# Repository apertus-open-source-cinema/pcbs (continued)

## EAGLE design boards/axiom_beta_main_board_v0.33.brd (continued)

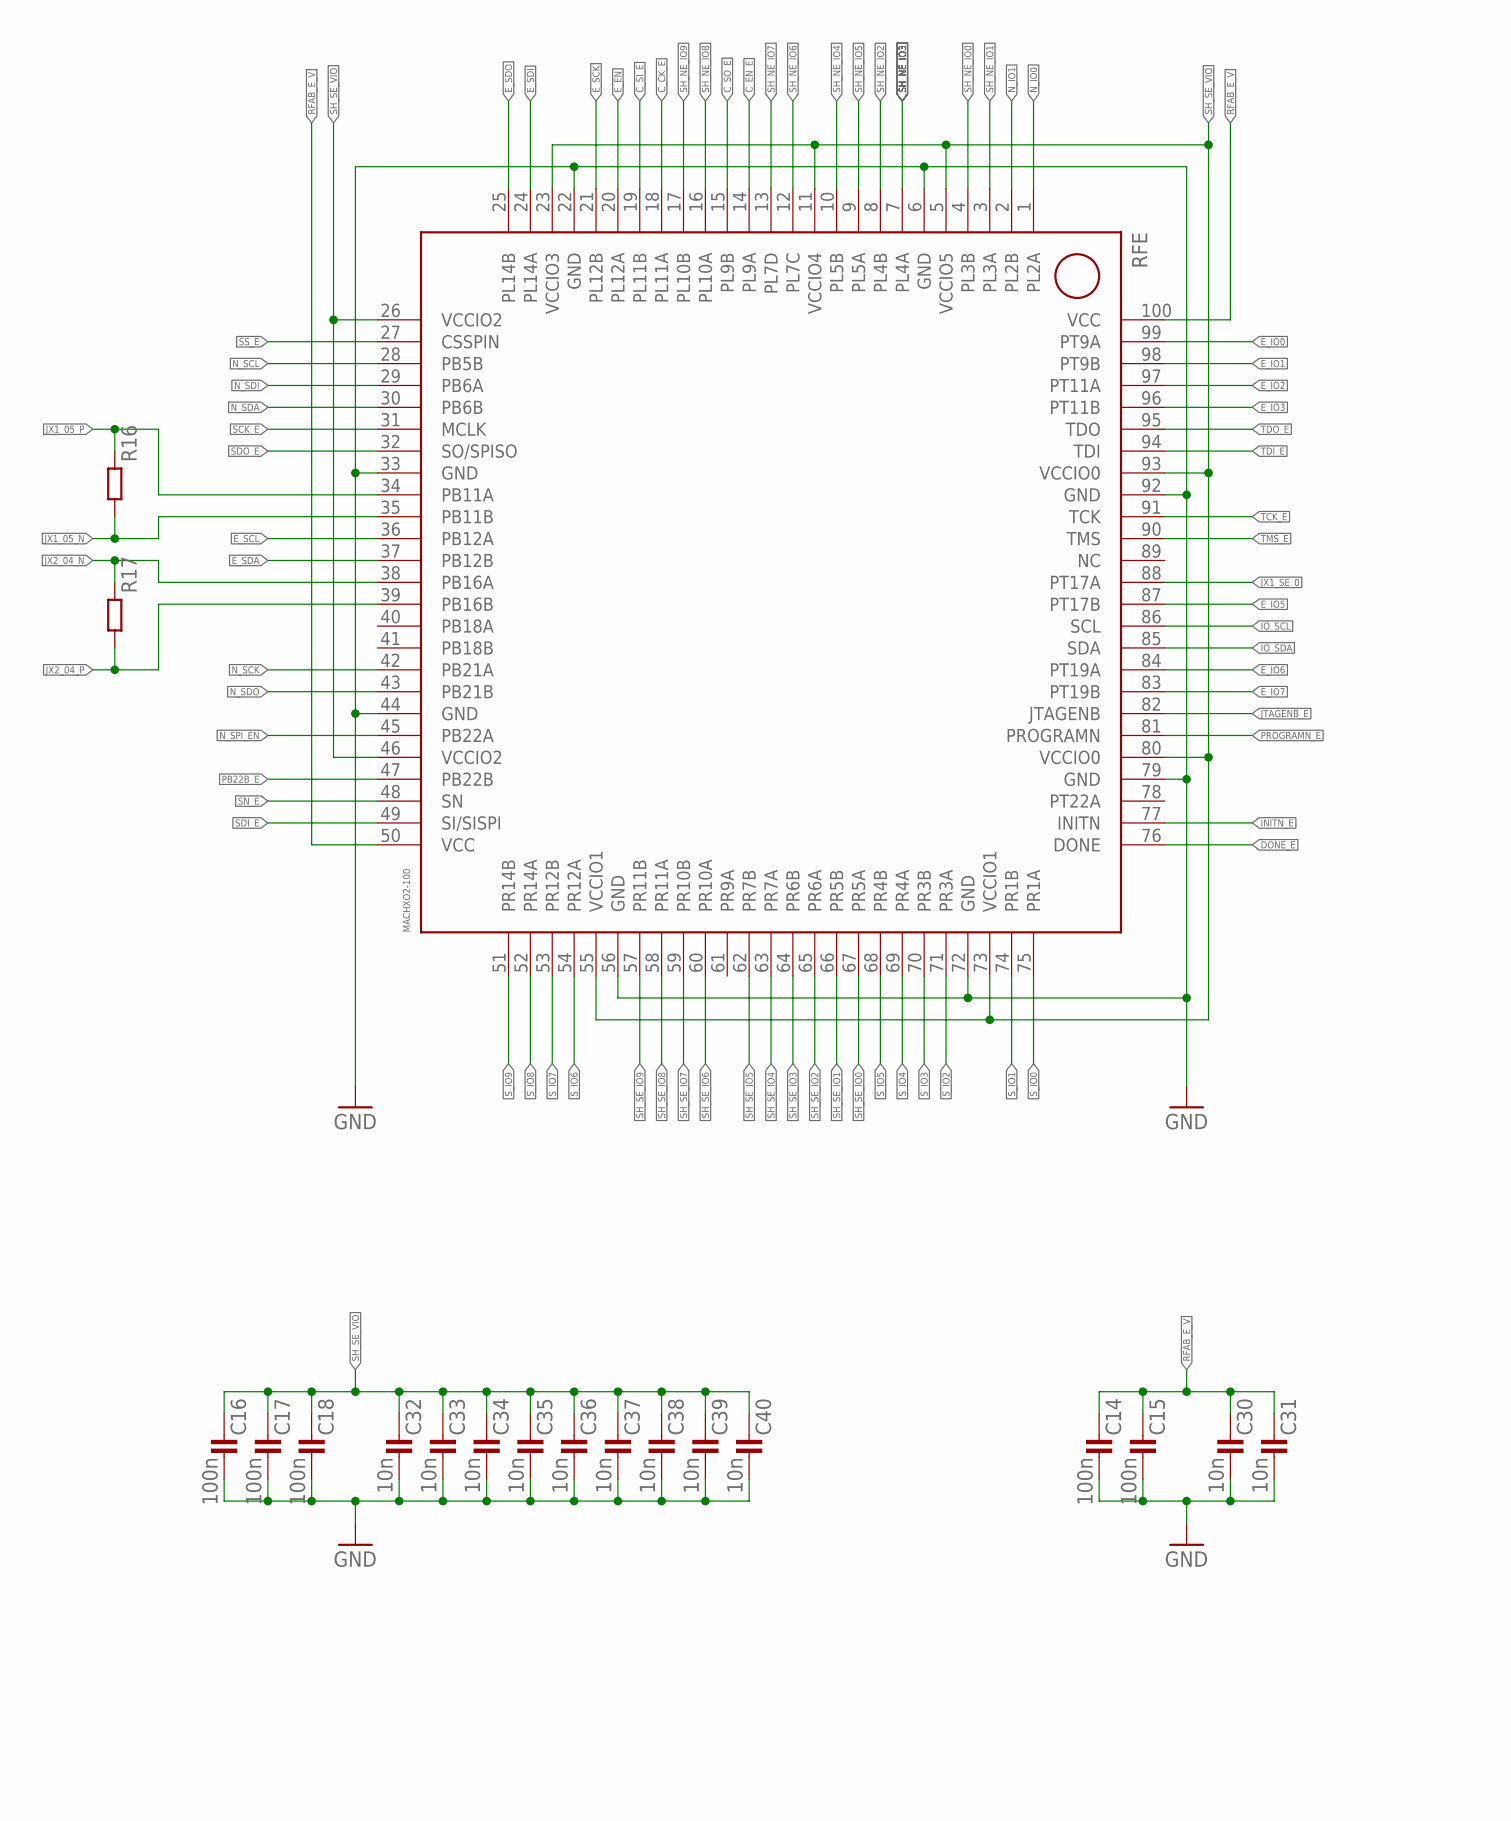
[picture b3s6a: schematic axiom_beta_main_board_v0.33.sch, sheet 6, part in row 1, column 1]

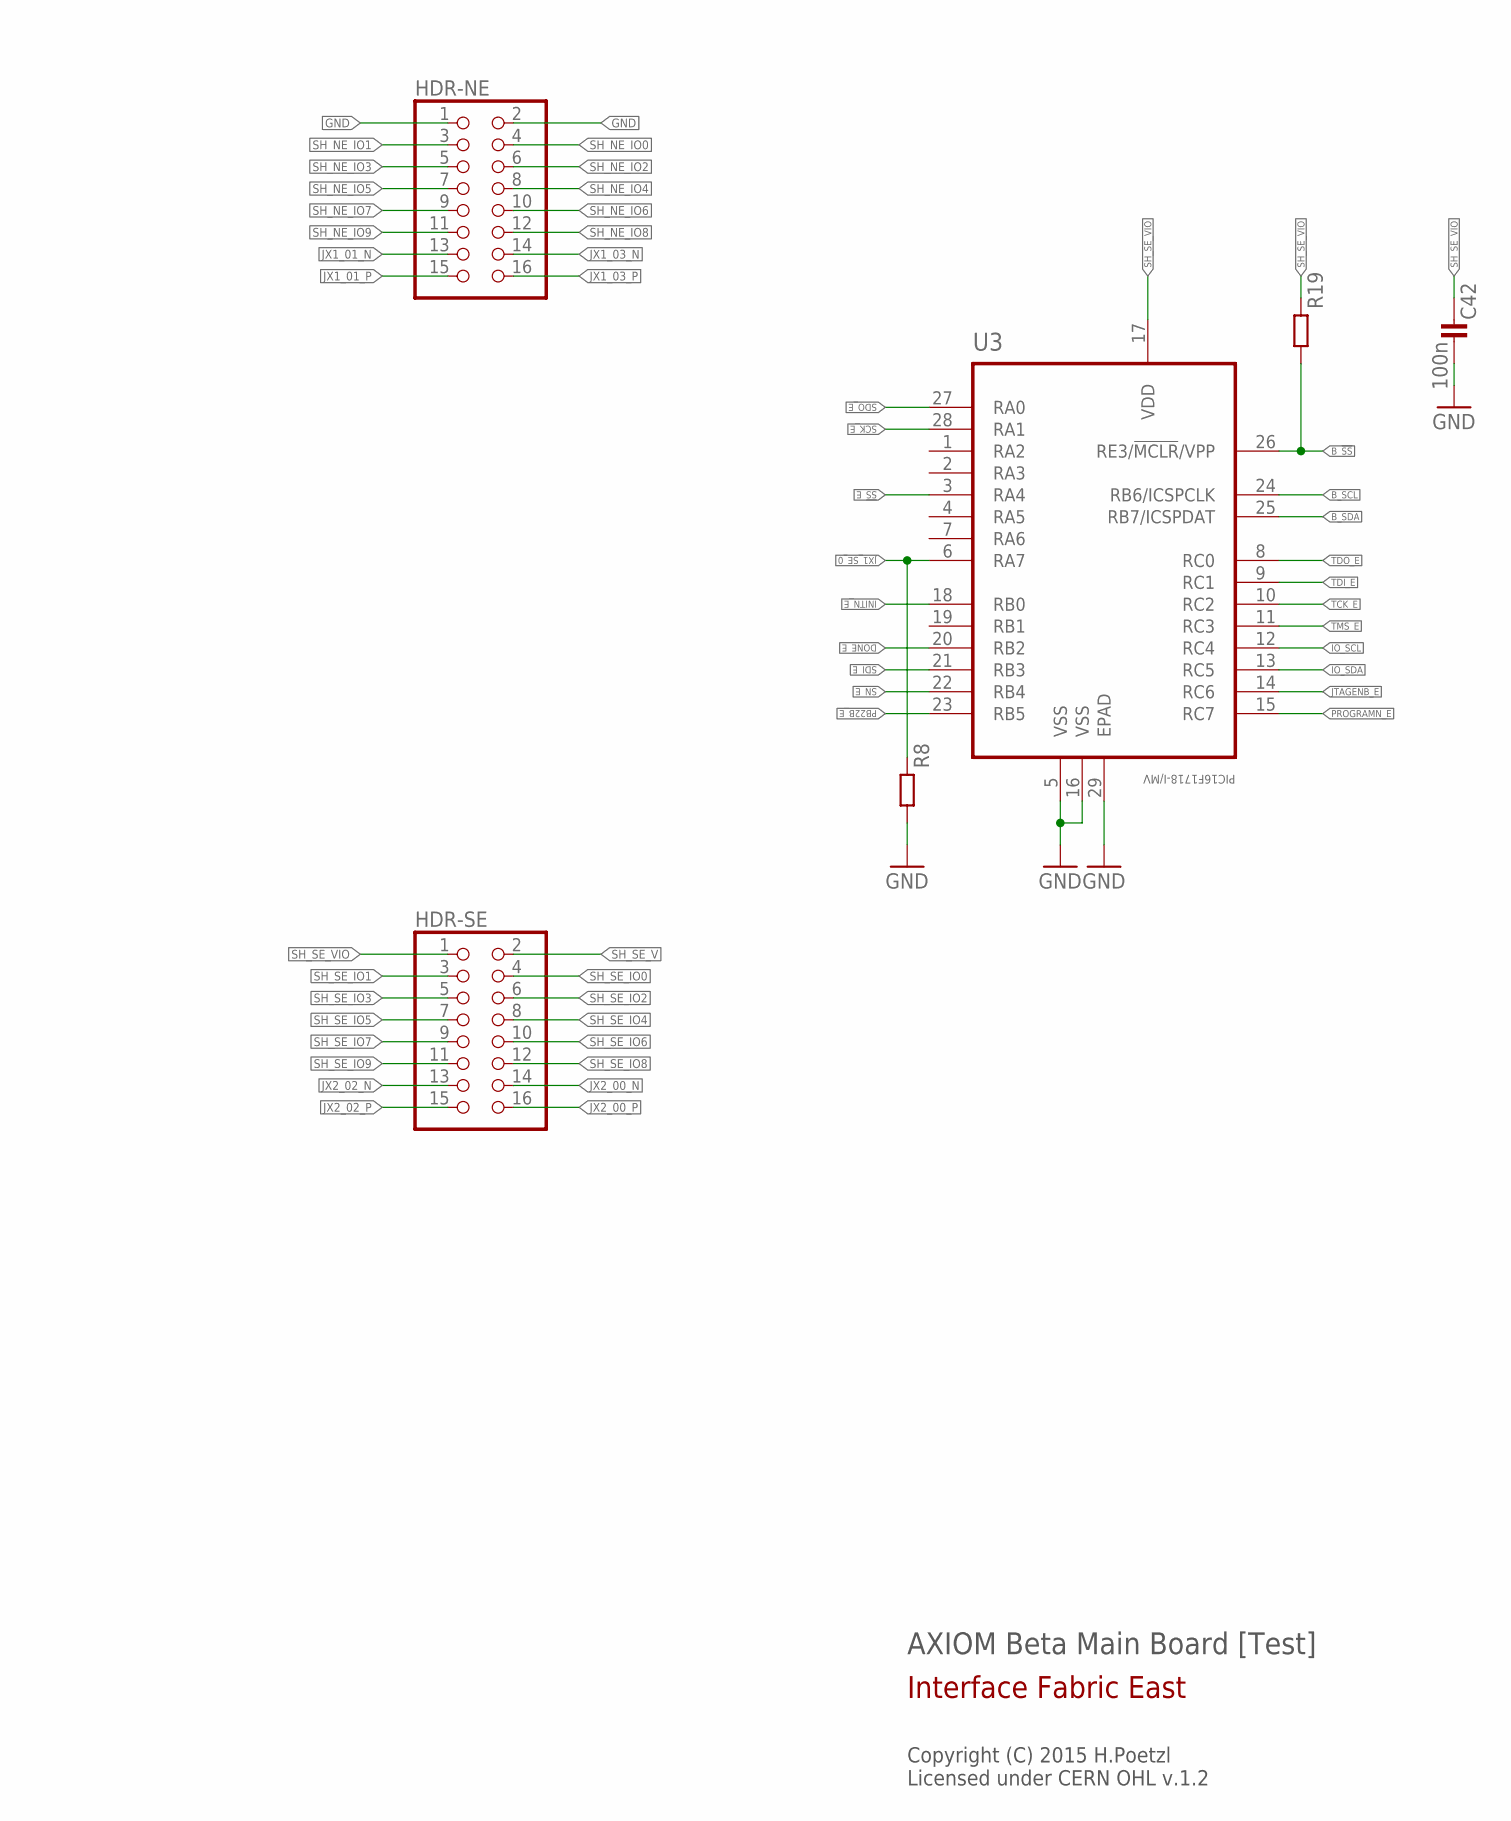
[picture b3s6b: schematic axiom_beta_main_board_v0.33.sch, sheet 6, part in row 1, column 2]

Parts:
C14, C15, C16, C17, C18, C42: 100n; 0402-B
C30, C31, C32, C33, C34, C35, C36, C37, C38, C39, C40: 10n; 0402-B
HDR-NE: PINHD-2X08_2.00_LPR; 62101621821
HDR-SE: PINHD-2X08_2.00_LPR; 62101621821
R8, R19: R0402-B; 0402-B
R16, R17: R0201-B; 0201-B
RFE: MACHXO2-100; MACHXO2-100TQFP
U3: PIC16F1718-I/MV; QFN40P400X400X55-29N

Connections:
!SS!_E: RFE.27 (CSSPIN), U3.3 (RA4)
B_!SS: R19.2, U3.26 (RE3/!MCLR!/VPP); also elsewhere on the board
B_SCL: U3.24 (RB6/ICSPCLK); also elsewhere on the board
B_SDA: U3.25 (RB7/ICSPDAT); also elsewhere on the board
C_CK_E: RFE.18 (PL11A); also elsewhere on the board
C_EN_E: RFE.14 (PL9A); also elsewhere on the board
C_SI_E: RFE.19 (PL11B); also elsewhere on the board
C_SO_E: RFE.15 (PL9B); also elsewhere on the board
DONE_E: RFE.76 (DONE), U3.20 (RB2)
E_EN: RFE.20 (PL12A); also elsewhere on the board
E_IO0: RFE.99 (PT9A)
E_IO1: RFE.98 (PT9B)
E_IO2: RFE.97 (PT11A)
E_IO3: RFE.96 (PT11B)
E_IO5: RFE.87 (PT17B)
E_IO6: RFE.84 (PT19A)
E_IO7: RFE.83 (PT19B)
E_SCK: RFE.21 (PL12B); also elsewhere on the board
E_SCL: RFE.36 (PB12A); also elsewhere on the board
E_SDA: RFE.37 (PB12B); also elsewhere on the board
E_SDI: RFE.24 (PL14A); also elsewhere on the board
E_SDO: RFE.25 (PL14B); also elsewhere on the board
GND: C14.2, C15.2, C16.2, C17.2, C18.2, C30.2, C31.2, C32.2, C33.2, C34.2, C35.2, C36.2, C37.2, C38.2, C39.2, C40.2, C42.2, HDR-NE.1, HDR-NE.2, R8.2, RFE.6 (GND), RFE.22 (GND), RFE.33 (GND), RFE.44 (GND), RFE.56 (GND), RFE.72 (GND), RFE.79 (GND), RFE.92 (GND), U3.5 (VSS), U3.16 (VSS), U3.29 (EPAD); also elsewhere on the board
INITN_E: RFE.77 (INITN), U3.18 (RB0)
IO_SCL: RFE.86 (SCL), U3.12 (RC4)
IO_SDA: RFE.85 (SDA), U3.13 (RC5)
JTAGENB_E: RFE.82 (JTAGENB), U3.14 (RC6)
JX1_01_N: HDR-NE.13; also elsewhere on the board
JX1_01_P: HDR-NE.15; also elsewhere on the board
JX1_03_N: HDR-NE.14; also elsewhere on the board
JX1_03_P: HDR-NE.16; also elsewhere on the board
JX1_05_N: R16.2, RFE.35 (PB11B); also elsewhere on the board
JX1_05_P: R16.1, RFE.34 (PB11A); also elsewhere on the board
JX1_SE_0: R8.1, RFE.88 (PT17A), U3.6 (RA7); also elsewhere on the board
JX2_00_N: HDR-SE.14; also elsewhere on the board
JX2_00_P: HDR-SE.16; also elsewhere on the board
JX2_02_N: HDR-SE.13; also elsewhere on the board
JX2_02_P: HDR-SE.15; also elsewhere on the board
JX2_04_N: R17.1, RFE.38 (PB16A); also elsewhere on the board
JX2_04_P: R17.2, RFE.39 (PB16B); also elsewhere on the board
N_IO0: RFE.1 (PL2A); also elsewhere on the board
N_IO1: RFE.2 (PL2B)
N_SCK: RFE.42 (PB21A); also elsewhere on the board
N_SCL: RFE.28 (PB5B); also elsewhere on the board
N_SDA: RFE.30 (PB6B); also elsewhere on the board
N_SDI: RFE.29 (PB6A); also elsewhere on the board
N_SDO: RFE.43 (PB21B); also elsewhere on the board
N_SPI_EN: RFE.45 (PB22A); also elsewhere on the board
PB22B_E: RFE.47 (PB22B), U3.23 (RB5)
PROGRAMN_E: RFE.81 (PROGRAMN), U3.15 (RC7)
RFAB_E_V: C14.1, C15.1, C30.1, C31.1, RFE.50 (VCC), RFE.100 (VCC); also elsewhere on the board
SCK_E: RFE.31 (MCLK), U3.28 (RA1)
SDI_E: RFE.49 (SI/SISPI), U3.21 (RB3)
SDO_E: RFE.32 (SO/SPISO), U3.27 (RA0)
SH_NE_IO0: HDR-NE.4, RFE.4 (PL3B)
SH_NE_IO1: HDR-NE.3, RFE.3 (PL3A)
SH_NE_IO2: HDR-NE.6, RFE.8 (PL4B)
SH_NE_IO3: HDR-NE.5, RFE.7 (PL4A)
SH_NE_IO4: HDR-NE.8, RFE.10 (PL5B)
SH_NE_IO5: HDR-NE.7, RFE.9 (PL5A)
SH_NE_IO6: HDR-NE.10, RFE.12 (PL7C)
SH_NE_IO7: HDR-NE.9, RFE.13 (PL7D)
SH_NE_IO8: HDR-NE.12, RFE.16 (PL10A)
SH_NE_IO9: HDR-NE.11, RFE.17 (PL10B)
SH_SE_IO0: HDR-SE.4, RFE.67 (PR5A)
SH_SE_IO1: HDR-SE.3, RFE.66 (PR5B)
SH_SE_IO2: HDR-SE.6, RFE.65 (PR6A)
SH_SE_IO3: HDR-SE.5, RFE.64 (PR6B)
SH_SE_IO4: HDR-SE.8, RFE.63 (PR7A)
SH_SE_IO5: HDR-SE.7, RFE.62 (PR7B)
SH_SE_IO6: HDR-SE.10, RFE.60 (PR10A)
SH_SE_IO7: HDR-SE.9, RFE.59 (PR10B)
SH_SE_IO8: HDR-SE.12, RFE.58 (PR11A)
SH_SE_IO9: HDR-SE.11, RFE.57 (PR11B)
SH_SE_V: HDR-SE.2; also elsewhere on the board
SH_SE_VIO: C16.1, C17.1, C18.1, C32.1, C33.1, C34.1, C35.1, C36.1, C37.1, C38.1, C39.1, C40.1, C42.1, HDR-SE.1, R19.1, RFE.5 (VCCIO5), RFE.11 (VCCIO4), RFE.23 (VCCIO3), RFE.26 (VCCIO2), RFE.46 (VCCIO2), RFE.55 (VCCIO1), RFE.73 (VCCIO1), RFE.80 (VCCIO0), RFE.93 (VCCIO0), U3.17 (VDD); also elsewhere on the board
SN_E: RFE.48 (SN), U3.22 (RB4)
S_IO0: RFE.75 (PR1A); also elsewhere on the board
S_IO1: RFE.74 (PR1B)
S_IO2: RFE.71 (PR3A)
S_IO3: RFE.70 (PR3B)
S_IO4: RFE.69 (PR4A)
S_IO5: RFE.68 (PR4B)
S_IO6: RFE.54 (PR12A)
S_IO7: RFE.53 (PR12B)
S_IO8: RFE.52 (PR14A)
S_IO9: RFE.51 (PR14B)
TCK_E: RFE.91 (TCK), U3.10 (RC2)
TDI_E: RFE.94 (TDI), U3.9 (RC1)
TDO_E: RFE.95 (TDO), U3.8 (RC0)
TMS_E: RFE.90 (TMS), U3.11 (RC3)

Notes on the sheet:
AXIOM Beta Main Board [Test]
Copyright (C) 2015 H.Poetzl Licensed under CERN OHL v.1.2
Interface Fabric East

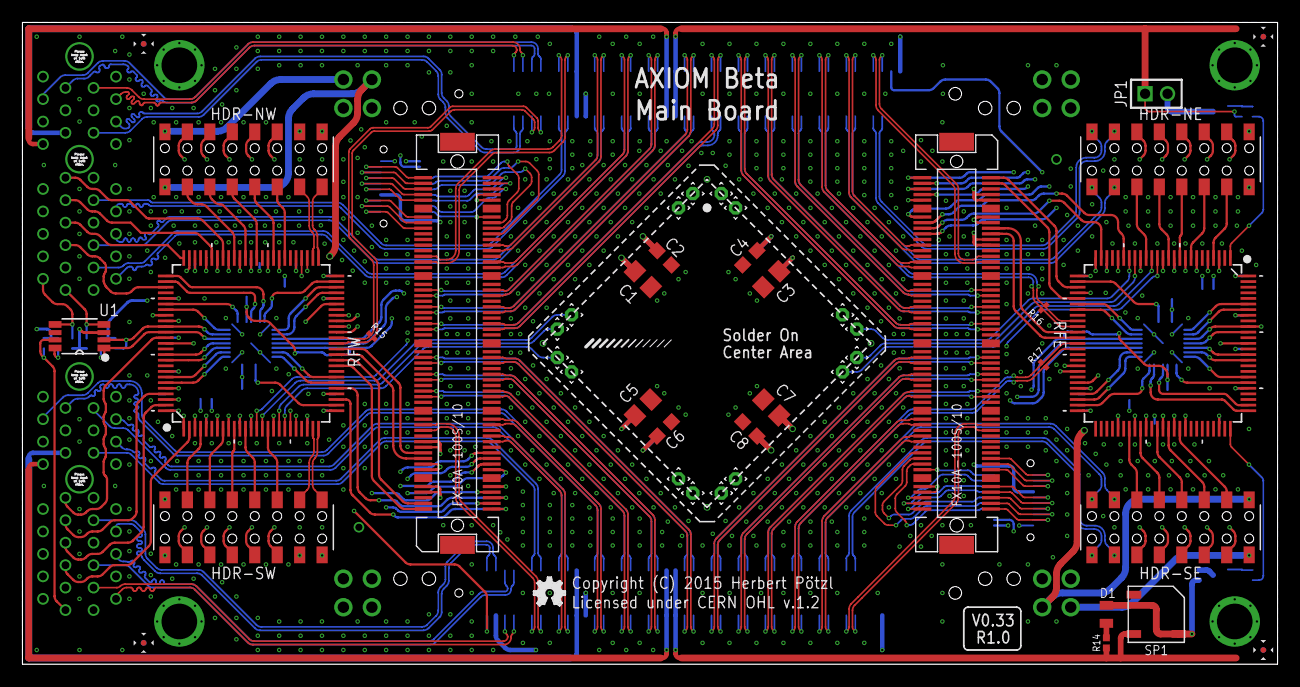
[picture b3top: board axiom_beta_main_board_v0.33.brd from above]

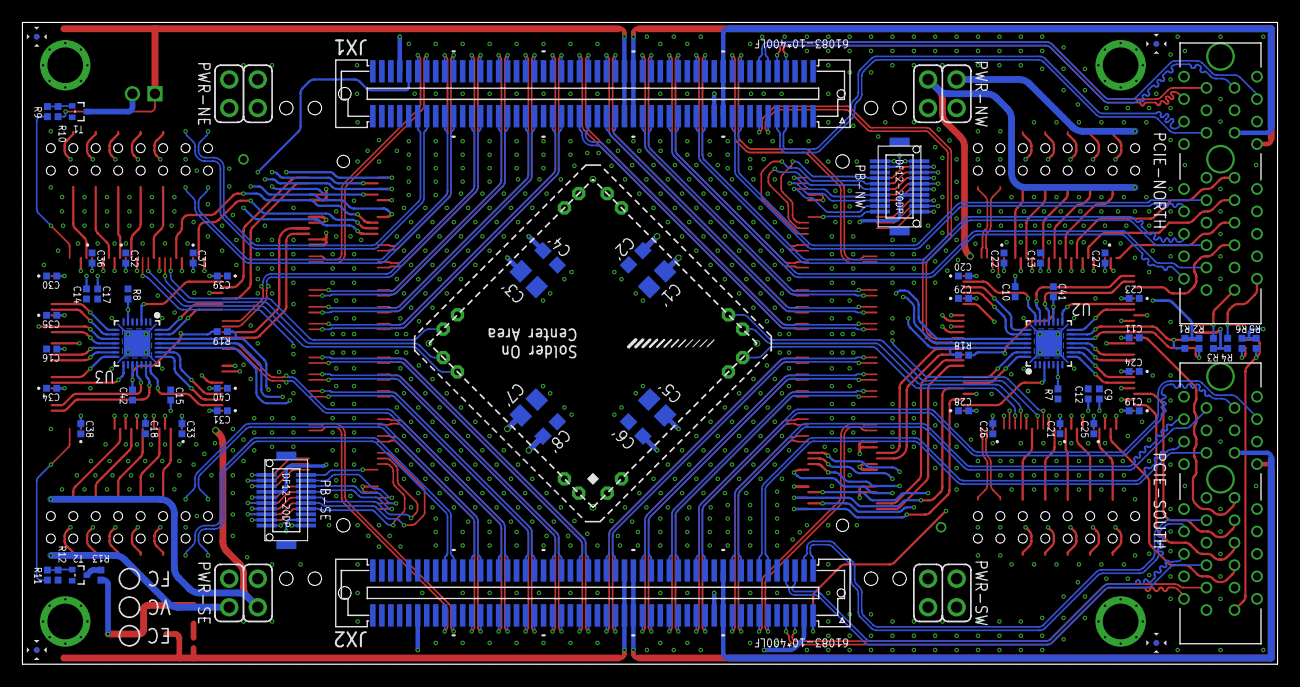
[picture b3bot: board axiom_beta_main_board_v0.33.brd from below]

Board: 4 copper layers, 111.8 x 57.1 mm, 111 parts (70 on the bottom side), 318 nets.

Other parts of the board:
LOGO1: OSHW_LOGO_FILLX0100-NT; OSHW_FILLX100_NOTEXT

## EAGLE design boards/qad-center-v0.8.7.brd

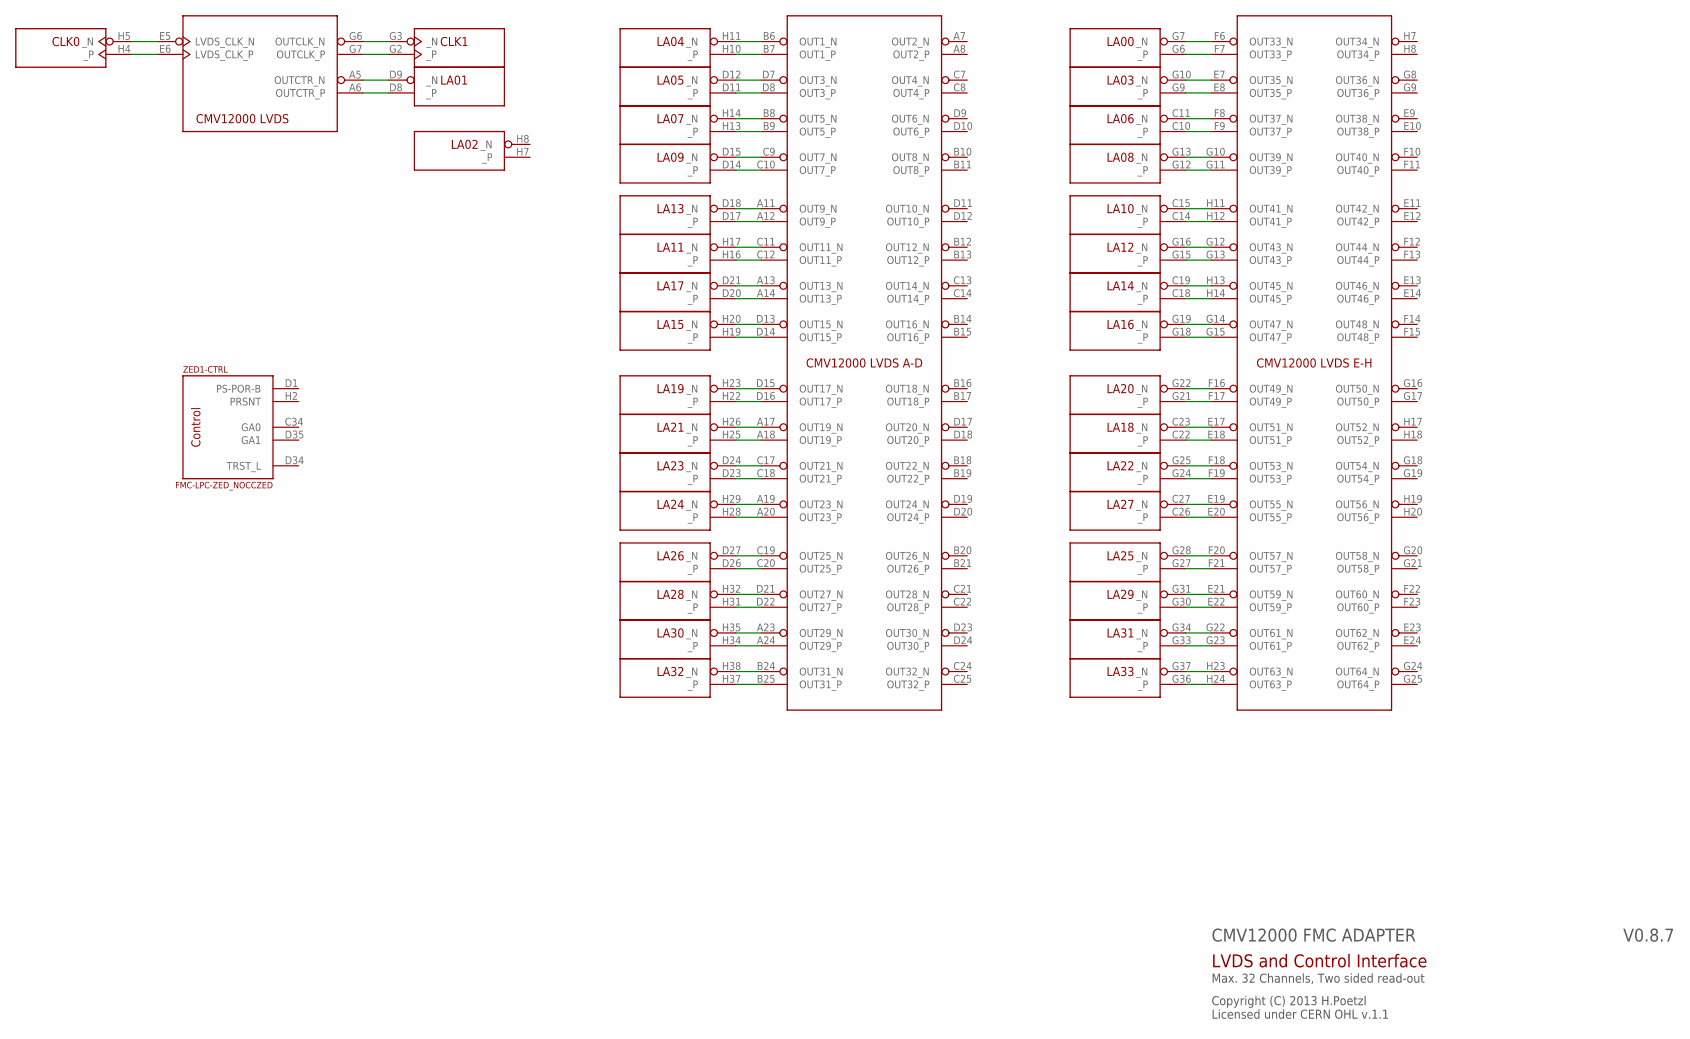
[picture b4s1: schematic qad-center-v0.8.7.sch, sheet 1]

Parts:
U$1: CMV12000ANDON+LM; 10-30-07-237-400T4+LM
ZED1: FMC-LPC-ZED_NOCCZED; ASP-134604-01-ZED

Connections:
unnamed: U$1.B6 (OUT1_N), ZED1.H11 (_N)
unnamed: U$1.B7 (OUT1_P), ZED1.H10 (_P)
unnamed: U$1.D7 (OUT3_N), ZED1.D12 (_N)
unnamed: U$1.D8 (OUT3_P), ZED1.D11 (_P)
unnamed: U$1.B8 (OUT5_N), ZED1.H14 (_N)
unnamed: U$1.C9 (OUT7_N), ZED1.D15 (_N)
unnamed: U$1.C10 (OUT7_P), ZED1.D14 (_P)
unnamed: U$1.G10 (OUT39_N), ZED1.G13 (_N)
unnamed: U$1.A11 (OUT9_N), ZED1.D18 (_N)
unnamed: U$1.A12 (OUT9_P), ZED1.D17 (_P)
unnamed: U$1.C11 (OUT11_N), ZED1.H17 (_N)
unnamed: U$1.C12 (OUT11_P), ZED1.H16 (_P)
unnamed: U$1.A13 (OUT13_N), ZED1.D21 (_N)
unnamed: U$1.A14 (OUT13_P), ZED1.D20 (_P)
unnamed: U$1.D13 (OUT15_N), ZED1.H20 (_N)
unnamed: U$1.D14 (OUT15_P), ZED1.H19 (_P)
unnamed: U$1.F16 (OUT49_N), ZED1.G22 (_N)
unnamed: U$1.F17 (OUT49_P), ZED1.G21 (_P)
unnamed: U$1.A17 (OUT19_N), ZED1.H26 (_N)
unnamed: U$1.A18 (OUT19_P), ZED1.H25 (_P)
unnamed: U$1.C17 (OUT21_N), ZED1.D24 (_N)
unnamed: U$1.C18 (OUT21_P), ZED1.D23 (_P)
unnamed: U$1.A19 (OUT23_N), ZED1.H29 (_N)
unnamed: U$1.A20 (OUT23_P), ZED1.H28 (_P)
unnamed: U$1.C19 (OUT25_N), ZED1.D27 (_N)
unnamed: U$1.C20 (OUT25_P), ZED1.D26 (_P)
unnamed: U$1.D21 (OUT27_N), ZED1.H32 (_N)
unnamed: U$1.D22 (OUT27_P), ZED1.H31 (_P)
unnamed: U$1.A23 (OUT29_N), ZED1.H35 (_N)
unnamed: U$1.A24 (OUT29_P), ZED1.H34 (_P)
unnamed: U$1.B24 (OUT31_N), ZED1.H38 (_N)
unnamed: U$1.B25 (OUT31_P), ZED1.H37 (_P)
unnamed: U$1.D15 (OUT17_N), ZED1.H23 (_N)
unnamed: U$1.D16 (OUT17_P), ZED1.H22 (_P)
unnamed: U$1.G22 (OUT61_N), ZED1.G34 (_N)
unnamed: U$1.G23 (OUT61_P), ZED1.G33 (_P)
unnamed: U$1.E22 (OUT59_P), ZED1.G30 (_P)
unnamed: U$1.E21 (OUT59_N), ZED1.G31 (_N)
unnamed: U$1.F21 (OUT57_P), ZED1.G27 (_P)
unnamed: U$1.F20 (OUT57_N), ZED1.G28 (_N)
unnamed: U$1.E20 (OUT55_P), ZED1.C26 (_P)
unnamed: U$1.E19 (OUT55_N), ZED1.C27 (_N)
unnamed: U$1.F19 (OUT53_P), ZED1.G24 (_P)
unnamed: U$1.F18 (OUT53_N), ZED1.G25 (_N)
unnamed: U$1.E18 (OUT51_P), ZED1.C22 (_P)
unnamed: U$1.E17 (OUT51_N), ZED1.C23 (_N)
unnamed: U$1.H23 (OUT63_N), ZED1.G37 (_N)
unnamed: U$1.H24 (OUT63_P), ZED1.G36 (_P)
unnamed: U$1.G15 (OUT47_P), ZED1.G18 (_P)
unnamed: U$1.G14 (OUT47_N), ZED1.G19 (_N)
unnamed: U$1.H14 (OUT45_P), ZED1.C18 (_P)
unnamed: U$1.H13 (OUT45_N), ZED1.C19 (_N)
unnamed: U$1.G13 (OUT43_P), ZED1.G15 (_P)
unnamed: U$1.G12 (OUT43_N), ZED1.G16 (_N)
unnamed: U$1.H12 (OUT41_P), ZED1.C14 (_P)
unnamed: U$1.H11 (OUT41_N), ZED1.C15 (_N)
unnamed: U$1.G11 (OUT39_P), ZED1.G12 (_P)
unnamed: U$1.B9 (OUT5_P), ZED1.H13 (_P)
unnamed: U$1.F9 (OUT37_P), ZED1.C10 (_P)
unnamed: U$1.F8 (OUT37_N), ZED1.C11 (_N)
unnamed: U$1.E8 (OUT35_P), ZED1.G9 (_P)
unnamed: U$1.E7 (OUT35_N), ZED1.G10 (_N)
unnamed: U$1.F7 (OUT33_P), ZED1.G6 (_P)
unnamed: U$1.F6 (OUT33_N), ZED1.G7 (_N)
unnamed: U$1.E5 (LVDS_CLK_N), ZED1.H5 (_N)
unnamed: U$1.E6 (LVDS_CLK_P), ZED1.H4 (_P)
unnamed: U$1.G6 (OUTCLK_N), ZED1.G3 (_N)
unnamed: U$1.G7 (OUTCLK_P), ZED1.G2 (_P)
unnamed: U$1.A5 (OUTCTR_N), ZED1.D9 (_N)
unnamed: U$1.A6 (OUTCTR_P), ZED1.D8 (_P)

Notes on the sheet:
CMV12000 FMC ADAPTER
Copyright (C) 2013 H.Poetzl Licensed under CERN OHL v.1.1
LVDS and Control Interface
Max. 32 Channels, Two sided read-out

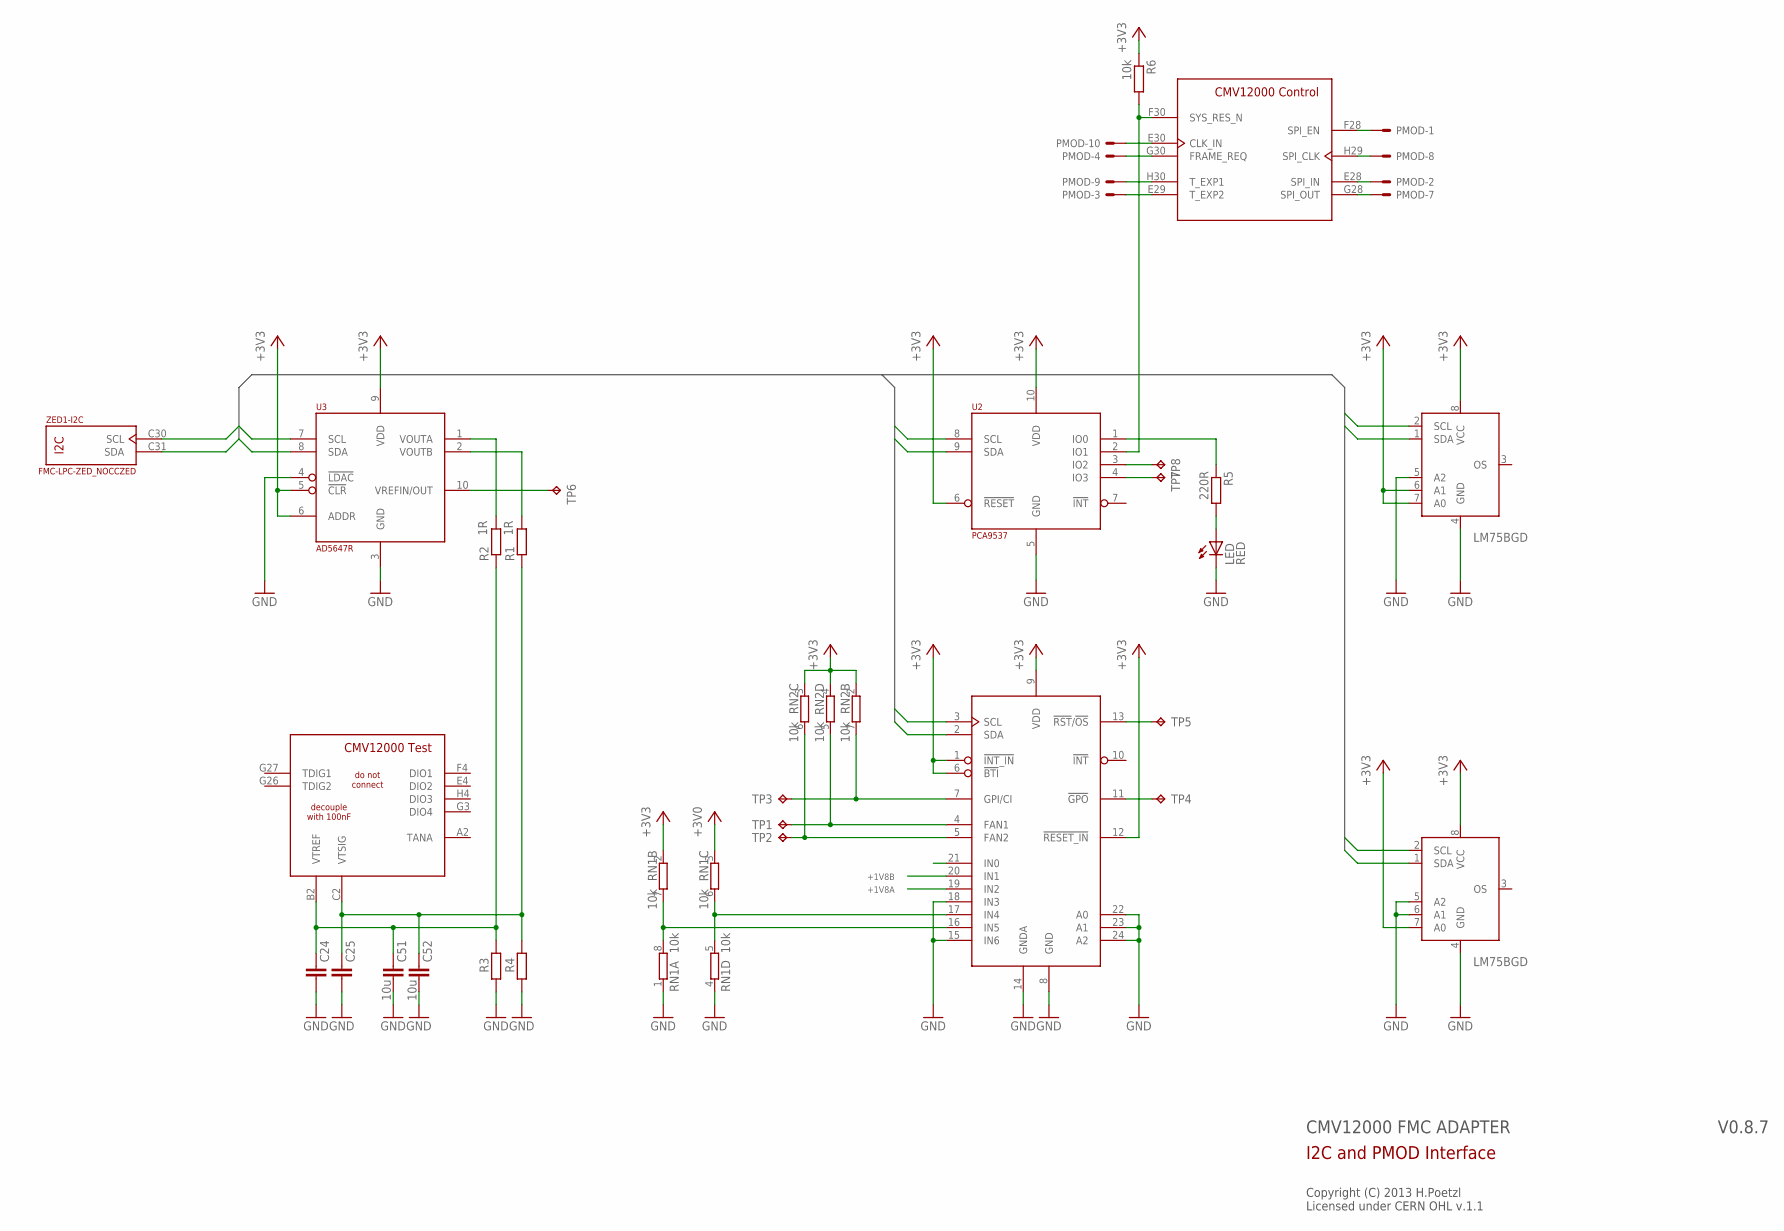
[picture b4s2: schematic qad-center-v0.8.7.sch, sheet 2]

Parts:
C24, C25: 100n; C0402
C51, C52: 10u; C0603K
LED: RED; CHIP-LED0603
PMOD: PMOD-8; 2X04/90/2MM
R1, R2: 1R; R0402
R3, R4: R-EU_R0402; R0402
R5: 220R; R0402
R6: 10k; R0402
RN1, RN2: 10k; CAT16
TP1, TP2, TP3, TP4, TP5, TP6, TP7, TP8: TPB1,27; B1,27
U1: LM96080; TSSOP24
U2: PCA9537; TSSOP-10
U3: AD5647R; SOP50P490X110-10N
U4, U5: LM75BGD; SOT996-2/3
U$1: CMV12000ANDON+LM; 10-30-07-237-400T4+LM
ZED1: FMC-LPC-ZED_NOCCZED; ASP-134604-01-ZED

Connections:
+1V8A: U1.19 (IN2); also elsewhere on the board
+1V8B: U1.20 (IN1); also elsewhere on the board
+3V0: RN1.3 (1); also elsewhere on the board
+3V3: R6.1, RN1.2 (1), RN2.2 (1), RN2.3 (1), RN2.4 (1), U1.1 (!INT_IN), U1.6 (!BTI), U1.9 (VDD), U1.12 (!RESET_IN), U2.6 (!RESET), U2.10 (VDD), U3.5 (!CLR), U3.6 (ADDR), U3.9 (VDD), U4.6 (A1), U4.7 (A0), U4.8 (VCC), U5.7 (A0), U5.8 (VCC); also elsewhere on the board
GND: C24.2, C25.2, C51.2, C52.2, LED.C, R3.2, R4.2, RN1.1, RN1.4 (1), U1.8 (GND), U1.14 (GNDA), U1.15 (IN6), U1.18 (IN3), U1.22 (A0), U1.23 (A1), U1.24 (A2), U2.5 (GND), U3.3 (GND), U3.4 (!LDAC), U4.4 (GND), U4.5 (A2), U5.4 (GND), U5.5 (A2), U5.6 (A1); also elsewhere on the board
unnamed: PMOD.1, U$1.F28 (SPI_EN)
unnamed: PMOD.8, U$1.H29 (SPI_CLK)
unnamed: PMOD.2, U$1.E28 (SPI_IN)
unnamed: PMOD.7, U$1.G28 (SPI_OUT)
unnamed: PMOD.10, U$1.E30 (CLK_IN)
unnamed: PMOD.4, U$1.G30 (FRAME_REQ)
unnamed: R1.2, U3.2 (VOUTB)
unnamed: PMOD.9, U$1.H30 (T_EXP1)
unnamed: PMOD.3, U$1.E29 (T_EXP2)
unnamed: RN2.5 (2), TP1.TP, U1.4 (FAN1)
unnamed: R6.2, U2.2 (IO1), U$1.F30 (SYS_RES_N)
unnamed: R5.1, U2.1 (IO0)
unnamed: RN2.6 (2), TP2.TP, U1.5 (FAN2)
unnamed: TP8.TP, U2.3 (IO2)
unnamed: TP7.TP, U2.4 (IO3)
unnamed: RN1.5 (2), RN1.6 (2), U1.17 (IN4)
unnamed: RN2.7 (2), TP3.TP, U1.7 (GPI/CI)
unnamed: TP4.TP, U1.11 (!GPO)
unnamed: TP5.TP, U1.13 (!RST!/!OS!)
unnamed: RN1.7 (2), RN1.8 (2), U1.16 (IN5)
unnamed: R2.2, U3.1 (VOUTA)
unnamed: LED.A, R5.2
unnamed: TP6.TP, U3.10 (VREFIN/OUT)
SCL: U1.3 (SCL), U2.8 (SCL), U3.7 (SCL), U4.2 (SCL), U5.2 (SCL), ZED1.C30 (SCL)
SDA: U1.2 (SDA), U2.9 (SDA), U3.8 (SDA), U4.1 (SDA), U5.1 (SDA), ZED1.C31 (SDA)
VTREF: C24.1, C51.1, R2.1, R3.1, U$1.B2 (VTREF)
VTSIG: C25.1, C52.1, R1.1, R4.1, U$1.C2 (VTSIG)

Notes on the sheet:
CMV12000 FMC ADAPTER
Copyright (C) 2013 H.Poetzl Licensed under CERN OHL v.1.1
I2C and PMOD Interface

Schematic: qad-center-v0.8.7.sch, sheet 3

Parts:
C1, C2, C3, C4, C5, C6, C7, C8, C9, C10, C11, C12, C13, C14, C15, C16, C17, C18, C19, C20, C21, C22, C23, C26, C27, C28, C29, C30, C31, C32, C33, C34, C35, C36, C37, C38, C39, C40, C41, C42, C43, C44, C45, C46, C47, C48, C49, C50: 100n; C0402
C53, C54, C55, C56: 10u; C0603K
C57, C58: 100u; C1210
C59, C60: 100u; C1210K
JP1, JP2, JP3, JP4: PINHD-1X02_2.54-S; 1X02-S
PWR: PINHD-1X02_2.54-S; 1X02-S
TP9, TP10, TP11, TP12: TPB1,27; B1,27
U6: MCP1826S-3002E/DB; SOT230P700X180-4N
U7: MCP1826S-1802E/DB; SOT230P700X180-4N
U8: AP1084TO252; TO252
U$1: CMV12000ANDON+LM; 10-30-07-237-400T4+LM
ZED1: FMC-LPC-ZED_NOCCZED; ASP-134604-01-ZED

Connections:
+1V8: C56.1, C57.1, JP2.2, JP3.2, JP4.2, U7.3 (VOUT)
+1V8A: C26.1, C27.1, C28.1, C29.1, C30.1, C48.1, JP3.1, TP9.TP, U$1.A10 (VDD18), U$1.A15 (VDD18), U$1.A16 (VDD18), U$1.A22 (VDD18), U$1.A26 (VDD18), U$1.A27 (VDD18), U$1.B4 (VDD18); also elsewhere on the board
+1V8B: C41.1, C42.1, C43.1, C44.1, C45.1, C46.1, C47.1, JP4.1, TP10.TP, U$1.E1 (VDD18_PLL), U$1.H5 (VDD18), U$1.H10 (VDD18), U$1.H15 (VDD18), U$1.H16 (VDD18), U$1.H22 (VDD18), U$1.H26 (VDD18); also elsewhere on the board
+3V0: C31.1, C32.1, C33.1, C34.1, C35.1, C54.1, TP11.TP, U6.3 (VOUT), U$1.A30 (VDD_PIX), U$1.D28 (VDD_PIX), U$1.D30 (VDD_PIX), U$1.G1 (VDD_PIX), U$1.H28 (VDD_PIX); also elsewhere on the board
+3V3: C17.1, C18.1, C19.1, C20.1, C21.1, C22.1, C23.1, C36.1, C37.1, C38.1, C39.1, C40.1, C49.1, C50.1, C53.1, C55.1, C58.1, C60.1, JP1.2, TP12.TP, U6.1 (VIN), U7.1 (VIN), U8.2 (VOUT), U$1.C26 (VDD33), U$1.C27 (VDD33), U$1.D3 (VDD33), U$1.D26 (VDD33), U$1.E2 (VDD_RES), U$1.E26 (VDD33), U$1.F5 (VDD33), U$1.F26 (VDD33), U$1.G4 (VDD_RES); also elsewhere on the board
+5V: C59.1, PWR.2, U8.3 (VIN)
GND: C1.2, C2.2, C3.2, C4.2, C5.2, C6.2, C7.2, C8.2, C9.2, C10.2, C11.2, C12.2, C13.2, C14.2, C15.2, C16.2, C26.2, C27.2, C28.2, C29.2, C30.2, C31.2, C32.2, C33.2, C34.2, C35.2, C36.2, C37.2, C38.2, C39.2, C40.2, C41.2, C42.2, C43.2, C44.2, C45.2, C46.2, C47.2, C48.2, C49.2, C50.2, C53.2, C54.2, C55.2, C56.2, C57.2, C58.2, C59.2, C60.2, PWR.1, U6.2 (GND), U6.4 (GND(TAB)), U7.2 (GND), U7.4 (GND(TAB)), U8.1 (ADJ), U$1.A9 (GND), U$1.A21 (GND), U$1.A25 (GND), U$1.A28 (GND), U$1.A29 (GND), U$1.B5 (GND), U$1.B22 (GND), U$1.B26 (GND), U$1.B27 (GND), U$1.B28 (GND), U$1.C15 (GND), U$1.C16 (GND), U$1.C28 (GND), U$1.D2 (GND), U$1.D25 (GND), U$1.D27 (GND), U$1.D29 (GND), U$1.E3 (GND), U$1.E15 (GND), U$1.E16 (GND), U$1.E25 (GND), U$1.E27 (GND), U$1.F27 (GND), U$1.G5 (GND), U$1.H1 (GND), U$1.H6 (GND), U$1.H9 (GND), U$1.H21 (GND), U$1.H25 (GND), U$1.H27 (GND), ZED1.C1 (GND), ZED1.C4 (GND), ZED1.C5 (GND), ZED1.C8 (GND), ZED1.C9 (GND), ZED1.C12 (GND), ZED1.C13 (GND), ZED1.C16 (GND), ZED1.C17 (GND), ZED1.C20 (GND), ZED1.C21 (GND), ZED1.C24 (GND), ZED1.C25 (GND), ZED1.C28 (GND), ZED1.C29 (GND), ZED1.C32 (GND), ZED1.C33 (GND), ZED1.C36 (GND), ZED1.C38 (GND), ZED1.C40 (GND), ZED1.D2 (GND), ZED1.D3 (GND), ZED1.D6 (GND), ZED1.D7 (GND), ZED1.D10 (GND), ZED1.D13 (GND), ZED1.D16 (GND), ZED1.D19 (GND), ZED1.D22 (GND), ZED1.D25 (GND), ZED1.D28 (GND), ZED1.D37 (GND), ZED1.D39 (GND), ZED1.G1 (GND), ZED1.G4 (GND), ZED1.G5 (GND), ZED1.G8 (GND), ZED1.G11 (GND), ZED1.G14 (GND), ZED1.G17 (GND), ZED1.G20 (GND), ZED1.G23 (GND), ZED1.G26 (GND), ZED1.G29 (GND), ZED1.G32 (GND), ZED1.G35 (GND), ZED1.G38 (GND), ZED1.G40 (GND), ZED1.H3 (GND), ZED1.H6 (GND), ZED1.H9 (GND), ZED1.H12 (GND), ZED1.H15 (GND), ZED1.H18 (GND), ZED1.H21 (GND), ZED1.H24 (GND), ZED1.H27 (GND), ZED1.H30 (GND), ZED1.H33 (GND), ZED1.H36 (GND), ZED1.H39 (GND); also elsewhere on the board
unnamed: C17.2, U$1.F2 (CMDP)
unnamed: C18.2, U$1.B1 (CMD_COL_LOAD)
unnamed: C19.2, U$1.B29 (CMD_RAMP)
unnamed: C20.2, U$1.C6 (CMD_COLAMP)
unnamed: C21.2, U$1.D1 (CMD_COL_PC)
unnamed: C22.2, U$1.F3 (CMDP_COMP_INV)
unnamed: C23.2, U$1.H3 (CMDP_COMP)
unnamed: C1.1, U$1.G2 (VCLAMP_ADC)
unnamed: C2.1, U$1.F1 (CMDN)
unnamed: C3.1, U$1.C1 (CMD_LVDS)
unnamed: C4.1, U$1.D4 (VCLAMP)
unnamed: C5.1, U$1.C29 (VBGAP)
unnamed: C6.1, U$1.C4 (VPCH_H)
unnamed: C7.1, U$1.A4 (VPCH_L)
unnamed: C8.1, U$1.B3 (VREF_ADC)
unnamed: C9.1, U$1.A3 (VREF)
unnamed: C10.1, U$1.D5 (VRES_L)
unnamed: C11.1, U$1.G29 (VRAMP1)
unnamed: C12.1, U$1.F29 (VRAMP2)
unnamed: C13.1, U$1.C5 (VTF_LOW0)
unnamed: C14.1, U$1.D6 (VTF_LOW1)
unnamed: C15.1, U$1.B30 (VTF_LOW2)
unnamed: C16.1, U$1.C30 (VTF_LOW3)
unnamed: ZED1.C35 (12V0), ZED1.C37 (12V0)
unnamed: JP1.1, ZED1.C39 (VCC33), ZED1.D32 (VCC33), ZED1.D36 (VCC33), ZED1.D38 (VCC33), ZED1.D40 (VCC33)
unnamed: JP2.1, ZED1.G39 (VADJ), ZED1.H40 (VADJ)

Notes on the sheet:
CMV12000 FMC ADAPTER
Copyright (C) 2013 H.Poetzl Licensed under CERN OHL v.1.1
Power and Decoupling

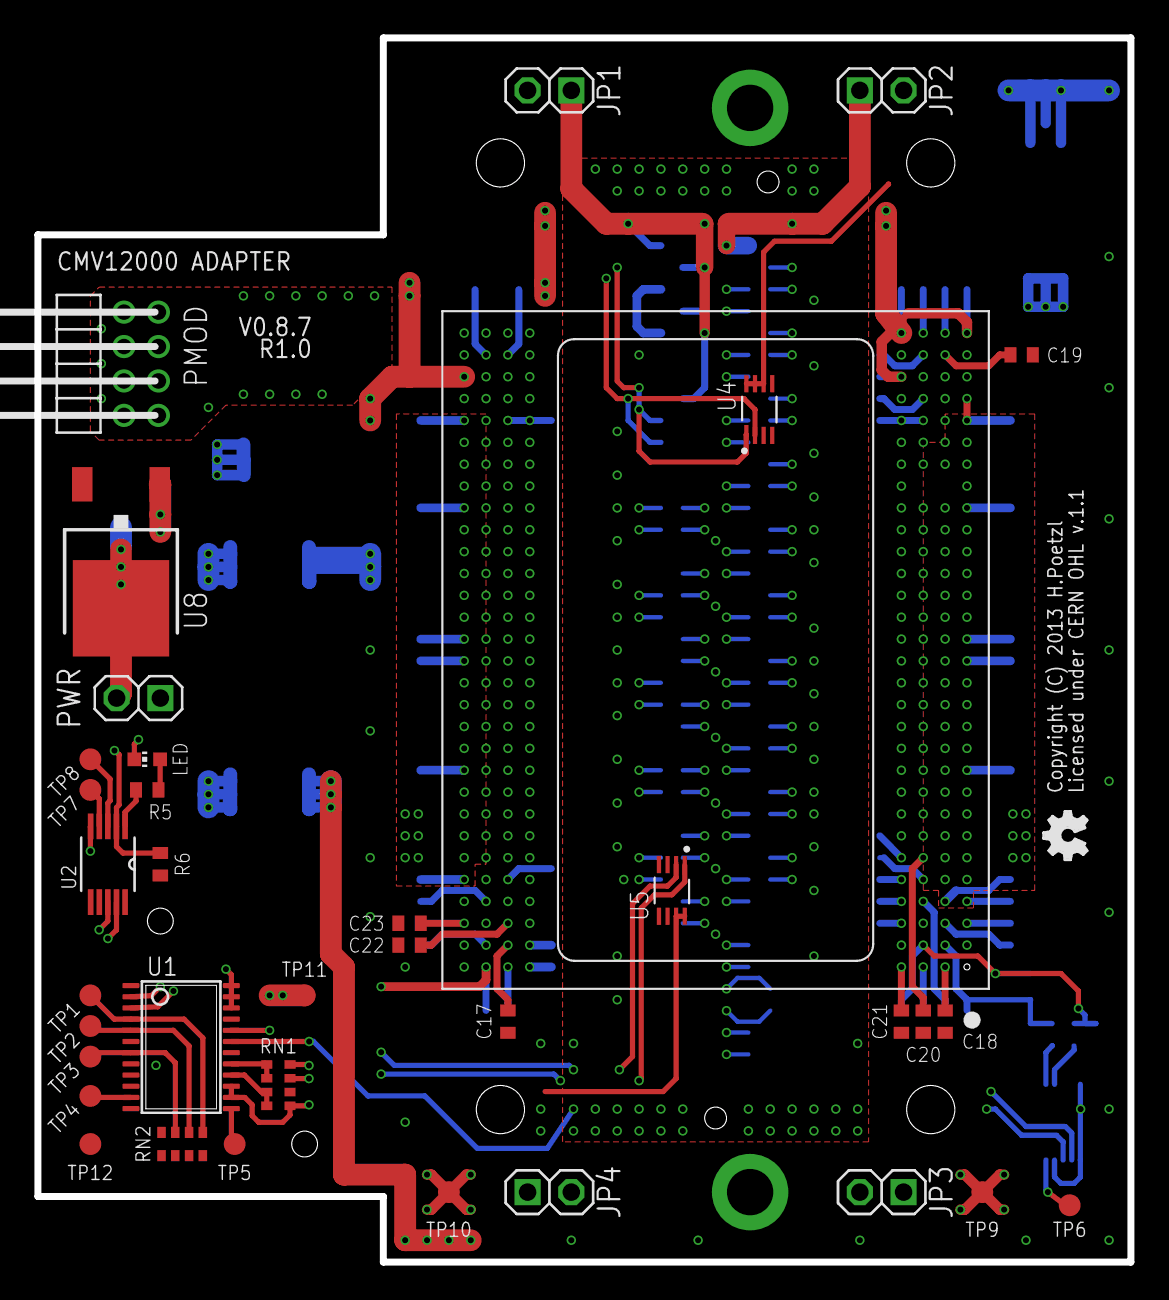
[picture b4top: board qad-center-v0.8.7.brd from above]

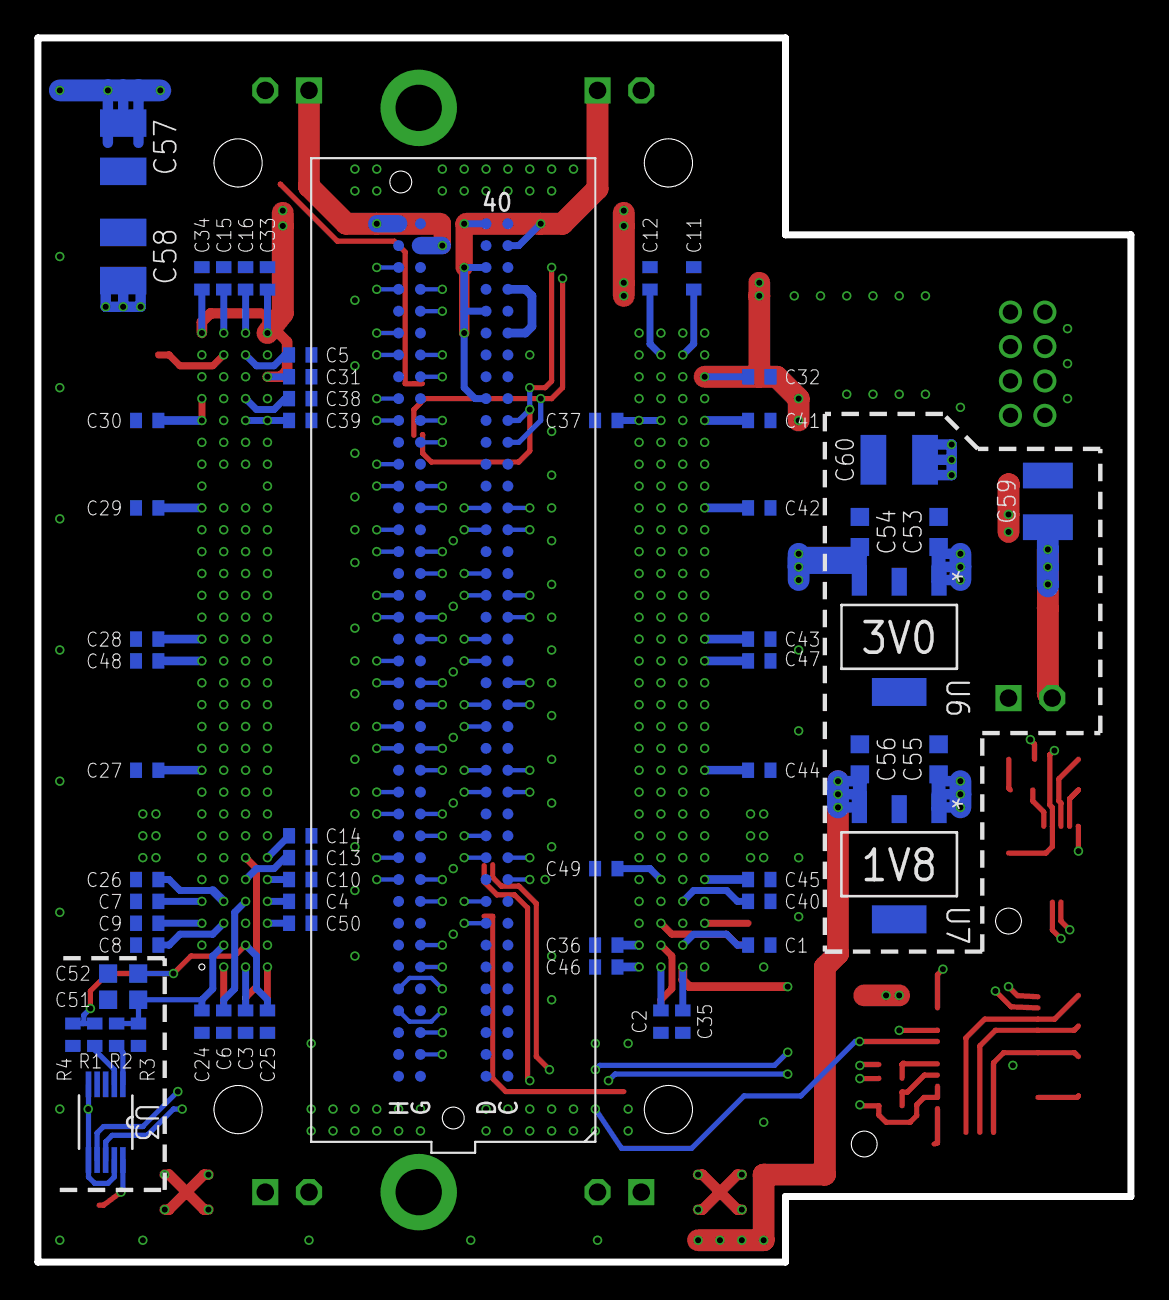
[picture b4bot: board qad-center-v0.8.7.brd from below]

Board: 4 copper layers, 63.5 x 71.1 mm, 98 parts (60 on the bottom side), 130 nets.

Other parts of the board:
U$5: OSHW_FILLX100_NOTEXT
